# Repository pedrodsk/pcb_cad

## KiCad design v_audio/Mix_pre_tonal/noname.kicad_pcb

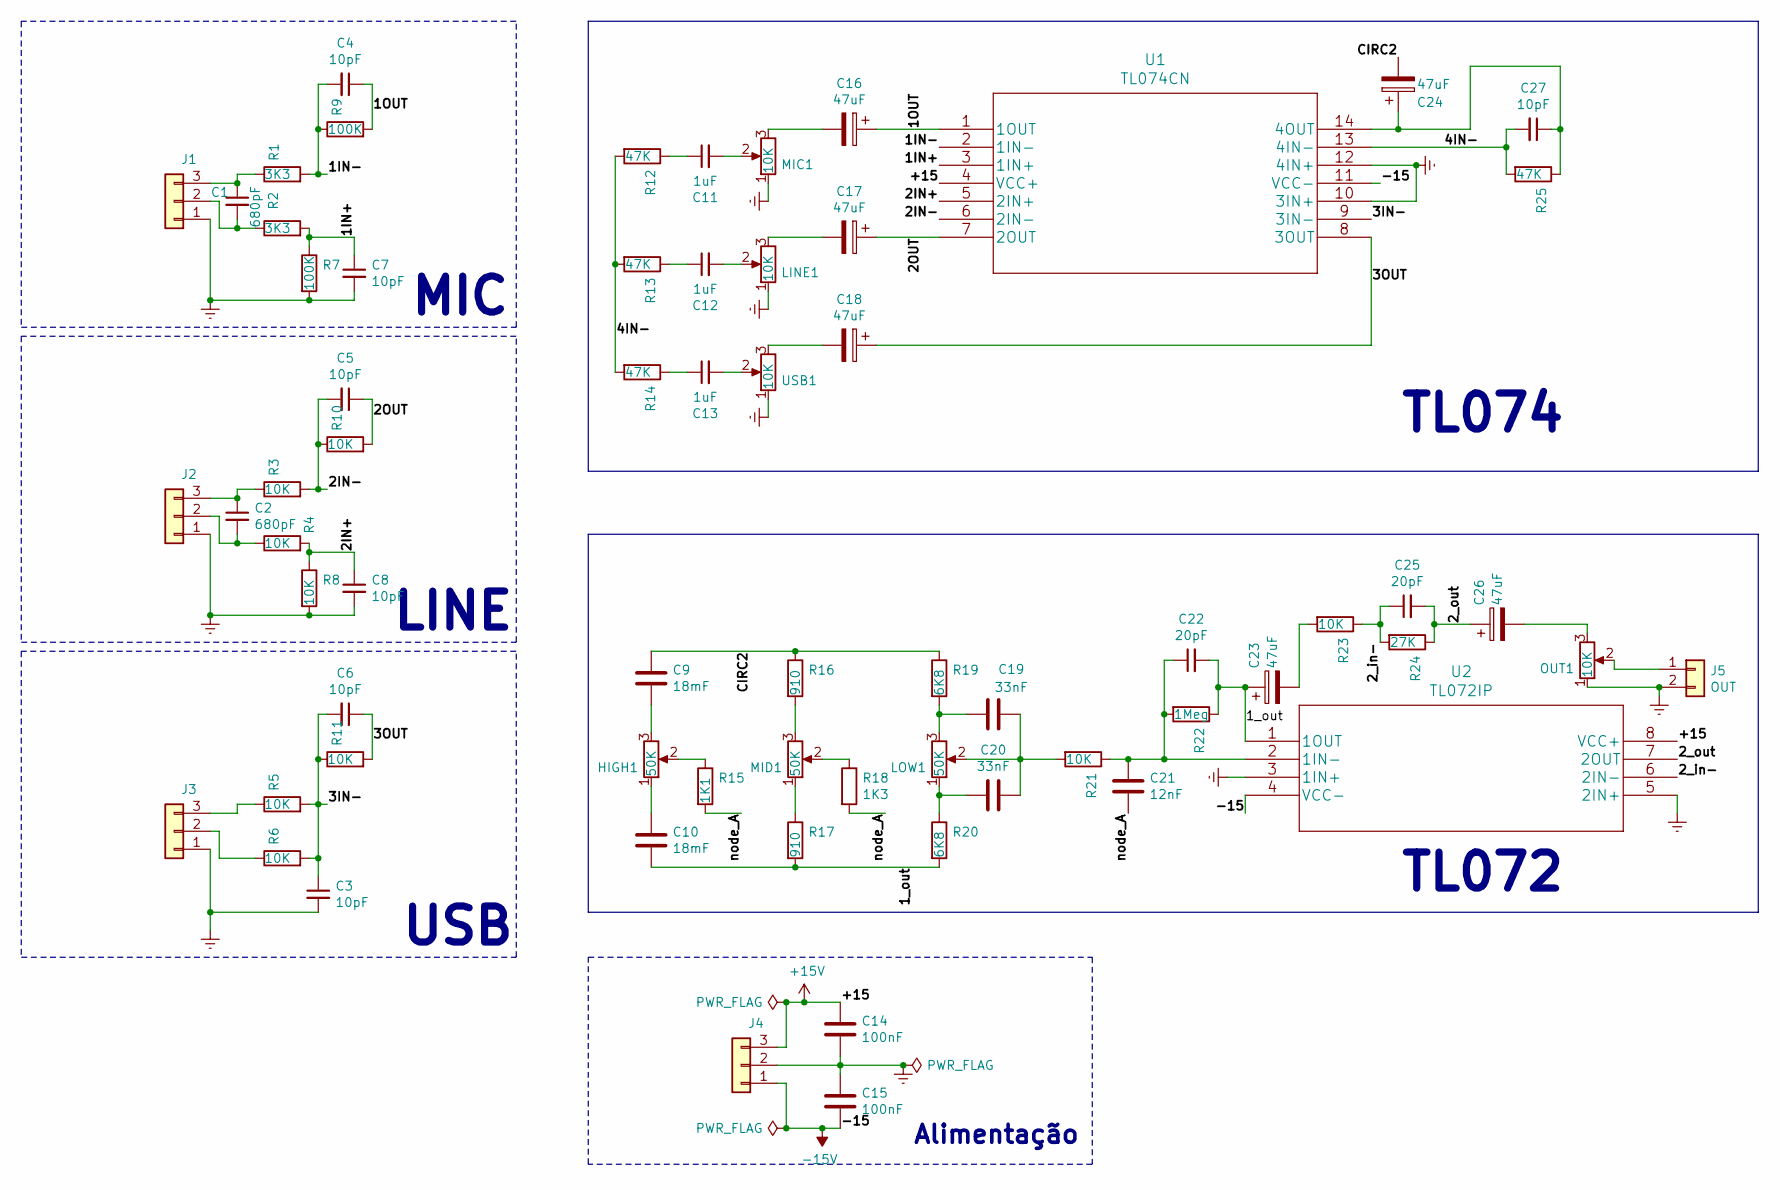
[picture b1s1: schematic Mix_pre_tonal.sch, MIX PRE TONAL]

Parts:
C1, C2: 680pF; C_Disc_D3.0mm_W1.6mm_P2.50mm
C3, C4, C5, C6, C7, C8, C27: 10pF; C_Disc_D3.0mm_W1.6mm_P2.50mm
C9, C10: 18mF; C_Disc_D7.0mm_W2.5mm_P5.00mm
C11, C12, C13: 1uF; C_Disc_D3.0mm_W1.6mm_P2.50mm
C14, C15: 100nF; C_Disc_D7.0mm_W2.5mm_P5.00mm
C16, C17, C18, C23, C24, C26: 47uF; CP_Radial_D4.0mm_P1.50mm
C19, C20: 33nF; C_Disc_D7.0mm_W2.5mm_P5.00mm
C21: 12nF; C_Disc_D7.0mm_W2.5mm_P5.00mm
C22, C25: 20pF; C_Disc_D3.0mm_W1.6mm_P2.50mm
HIGH1: 50K; Pot
J1: MIC; JST_NV_B03P-NV_1x03_P5.00mm_Vertical
J2: LINE; JST_NV_B03P-NV_1x03_P5.00mm_Vertical
J3: USB; JST_NV_B03P-NV_1x03_P5.00mm_Vertical
J4: Alimentação; JST_NV_B03P-NV_1x03_P5.00mm_Vertical
J5: OUT; JST_NV_B02P-NV_1x02_P5.00mm_Vertical
LINE1: 10K; Pot
LOW1: 50K; Pot
MIC1: 10K; Pot
MID1: 50K; Pot
OUT1: 10K; Pot
R1, R2: 3K3; R_Axial_DIN0207_L6.3mm_D2.5mm_P7.62mm_Horizontal
R3, R4, R5, R6, R8, R10, R11, R21, R23: 10K; R_Axial_DIN0207_L6.3mm_D2.5mm_P7.62mm_Horizontal
R7, R9: 100K; R_Axial_DIN0207_L6.3mm_D2.5mm_P7.62mm_Horizontal
R12, R13, R14, R25: 47K; R_Axial_DIN0207_L6.3mm_D2.5mm_P7.62mm_Horizontal
R15: 1K1; R_Axial_DIN0207_L6.3mm_D2.5mm_P7.62mm_Horizontal
R16, R17: 910; R_Axial_DIN0207_L6.3mm_D2.5mm_P7.62mm_Horizontal
R18: 1K3; R_Axial_DIN0207_L6.3mm_D2.5mm_P7.62mm_Horizontal
R19, R20: 6K8; R_Axial_DIN0207_L6.3mm_D2.5mm_P7.62mm_Horizontal
R22: 1Meg; R_Axial_DIN0207_L6.3mm_D2.5mm_P7.62mm_Horizontal
R24: 27K; R_Axial_DIN0207_L6.3mm_D2.5mm_P7.62mm_Horizontal
U1: TL074CN
U2: TL072IP
USB1: 10K; Pot

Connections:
+15V: C14.1, J4.3, U1.4 (VCC+), U2.8 (VCC+)
-15V: C15.2, J4.1, U1.11 (VCC-), U2.4 (VCC-)
/1IN+: C7.1, R2.2, R7.1, U1.3 (1IN+)
/1IN-: C4.2, R1.2, R9.1, U1.2 (1IN-)
/1OUT: C4.1, C16.1, R9.2, U1.1 (1OUT)
/1_out: C10.2, C22.2, C23.1, R17.2, R20.2, R22.1, U2.1 (1OUT)
/2IN+: C8.1, R4.2, R8.1, U1.5 (2IN+)
/2IN-: C5.2, R3.2, R10.1, U1.6 (2IN-)
/2OUT: C5.1, C17.1, R10.2, U1.7 (2OUT)
/2_in-: C25.1, R23.1, R24.2, U2.6 (2IN-)
/2_out: C25.2, C26.1, R24.1, U2.7 (2OUT)
/3IN-: C3.1, C6.2, R5.2, R6.2, R11.1, U1.9 (3IN-)
/3OUT: C6.1, C18.1, R11.2, U1.8 (3OUT)
/4IN-: C27.2, R12.2, R13.2, R14.2, R25.2, U1.13 (4IN-)
/node_A: C21.1, R15.2, R18.2
GNDREF: C3.2, C7.2, C8.2, C14.2, C15.1, J1.1, J2.1, J3.1, J4.2, J5.2, LINE1.1, MIC1.1, OUT1.1, R7.2, R8.2, U1.10 (3IN+), U1.12 (4IN+), U2.3 (1IN+), U2.5 (2IN+), USB1.1
unnamed: C1.1, J1.3, R1.1
unnamed: C1.2, J1.2, R2.1
unnamed: C2.1, J2.3, R3.1
unnamed: C2.2, J2.2, R4.1
unnamed: C9.2, HIGH1.3
unnamed: C10.1, HIGH1.1
unnamed: C11.1, R12.1
unnamed: C11.2, MIC1.2
unnamed: C12.1, R13.1
unnamed: C12.2, LINE1.2
unnamed: C13.1, R14.1
unnamed: C13.2, USB1.2
unnamed: C16.2, MIC1.3
unnamed: C17.2, LINE1.3
unnamed: C18.2, USB1.3
unnamed: C19.1, C20.1, LOW1.2, R21.2
unnamed: C19.2, LOW1.3, R19.2
unnamed: C20.2, LOW1.1, R20.1
unnamed: C21.2, C22.1, R21.1, R22.2, U2.2 (1IN-)
unnamed: C23.2, R23.2
unnamed: C26.2, OUT1.3
unnamed: HIGH1.2, R15.1
unnamed: J3.2, R6.1
unnamed: J3.3, R5.1
unnamed: J5.1, OUT1.2
unnamed: MID1.1, R17.1
unnamed: MID1.2, R18.1
unnamed: MID1.3, R16.2

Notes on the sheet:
MIC
LINE
USB
TL074
TL072
Alimentação

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
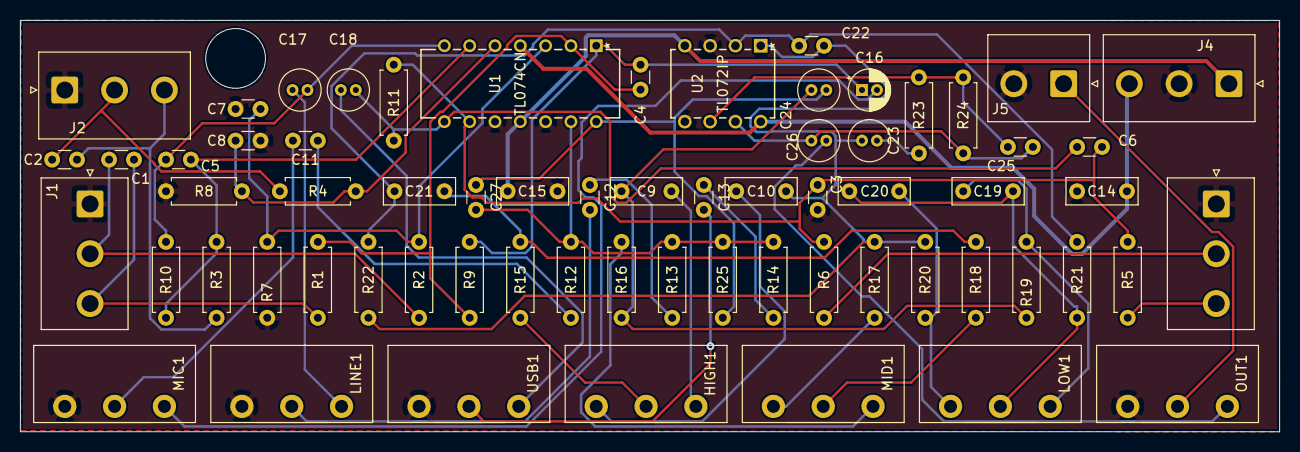
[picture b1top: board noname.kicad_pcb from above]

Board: 2 copper layers, 126.4 x 41.3 mm, 66 parts (0 on the bottom side), 46 nets.

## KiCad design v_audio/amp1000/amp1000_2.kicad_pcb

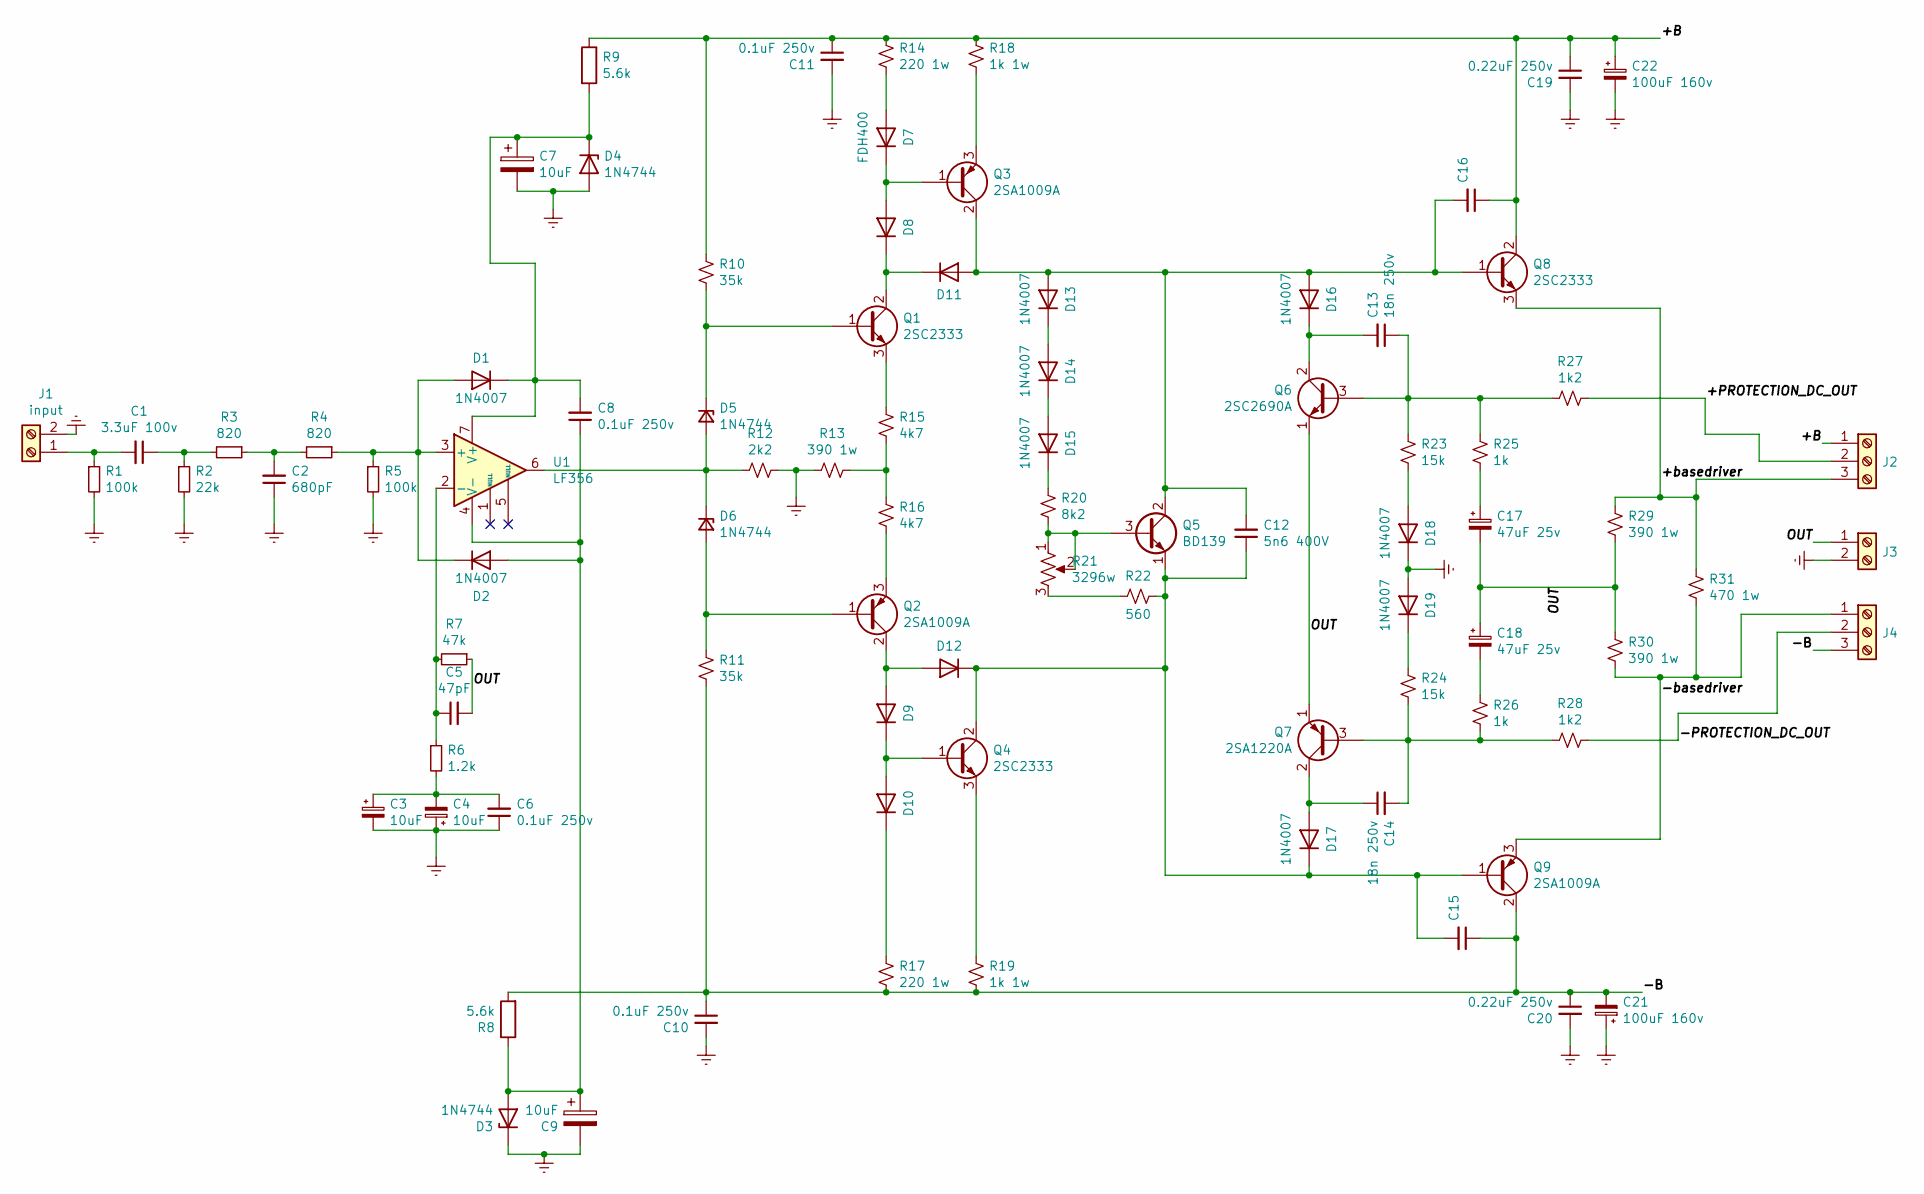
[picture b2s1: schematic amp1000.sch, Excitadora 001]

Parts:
C1: 3.3uF 100v; C_Axial_L22.0mm_D9.5mm_P27.50mm_Horizontal
C2: 680pF; C_Disc_D5.0mm_W2.5mm_P5.00mm
C3, C4, C7, C9: 10uF; CP_Radial_D4.0mm_P2.00mm
C5: 47pF; C_Disc_D5.0mm_W2.5mm_P5.00mm
C6, C8: 0.1uF 250v; C_Disc_D5.0mm_W2.5mm_P5.00mm
C10, C11: 0.1uF 250v; C_Disc_D7.5mm_W5.0mm_P10.00mm
C12: 5n6 400V; C_Disc_D5.0mm_W2.5mm_P5.00mm
C13, C14: 18n 250v; C_Disc_D5.0mm_W2.5mm_P5.00mm
C15, C16: 0.22uF 250v; C_Disc_D5.0mm_W2.5mm_P5.00mm
C17, C18: 47uF 25v; CP_Radial_D8.0mm_P3.50mm
C19, C20: 0.22uF 250v; C_Disc_D7.5mm_W5.0mm_P10.00mm
C21, C22: 100uF 160v; CP_Radial_D10.0mm_P5.00mm
D1, D2, D8, D9, D10, D11, D12, D13, D14, D15, D16, D17, D18, D19: 1N4007; D_A-405_P7.62mm_Horizontal
D3, D4, D5, D6: 1N4744; D_A-405_P7.62mm_Horizontal
D7: FDH400; D_A-405_P7.62mm_Horizontal
J1: input; TerminalBlock_bornier-2_P5.08mm
J2, J4: Screw_Terminal_01x03; TerminalBlock_bornier-3_P5.08mm
J3: Screw_Terminal_01x02; TerminalBlock_bornier-2_P5.08mm
Q1, Q4: 2SC2333; TO-220-3_Vertical
Q2, Q3: 2SA1009A; TO-220-3_Vertical
Q5: BD139; TO-126-3_Vertical
Q6: 2SC2690A; TO-126-3_Vertical
Q7: 2SA1220A; TO-126-3_Vertical
Q8: 2SC2333; TO-220-3_Horizontal_TabDown
Q9: 2SA1009A; TO-220-3_Horizontal_TabDown
R1, R5: 100k; R_Axial_DIN0207_L6.3mm_D2.5mm_P7.62mm_Horizontal
R2: 22k; R_Axial_DIN0207_L6.3mm_D2.5mm_P7.62mm_Horizontal
R3, R4: 820; R_Axial_DIN0207_L6.3mm_D2.5mm_P7.62mm_Horizontal
R6: 1.2k; R_Axial_DIN0207_L6.3mm_D2.5mm_P7.62mm_Horizontal
R7: 47k; R_Axial_DIN0207_L6.3mm_D2.5mm_P7.62mm_Horizontal
R8, R9: 5.6k; R_Axial_DIN0207_L6.3mm_D2.5mm_P7.62mm_Horizontal
R10, R11: 35k; R_Axial_DIN0207_L6.3mm_D2.5mm_P7.62mm_Horizontal
R12: 2k2; R_Axial_DIN0207_L6.3mm_D2.5mm_P7.62mm_Horizontal
R13, R29, R30: 390 1w; R_Axial_DIN0207_L6.3mm_D2.5mm_P7.62mm_Horizontal
R14, R17: 220 1w; R_Axial_DIN0207_L6.3mm_D2.5mm_P7.62mm_Horizontal
R15, R16: 4k7; R_Axial_DIN0207_L6.3mm_D2.5mm_P7.62mm_Horizontal
R18, R19: 1k 1w; R_Axial_DIN0207_L6.3mm_D2.5mm_P7.62mm_Horizontal
R20: 8k2; R_Axial_DIN0207_L6.3mm_D2.5mm_P7.62mm_Horizontal
R21: 3296w; Potentiometer_Bourns_3296W_Vertical
R22: 560; R_Axial_DIN0207_L6.3mm_D2.5mm_P7.62mm_Horizontal
R23, R24: 15k; R_Axial_DIN0207_L6.3mm_D2.5mm_P7.62mm_Horizontal
R25, R26: 1k; R_Axial_DIN0207_L6.3mm_D2.5mm_P7.62mm_Horizontal
R27, R28: 1k2; R_Axial_DIN0207_L6.3mm_D2.5mm_P7.62mm_Horizontal
R31: 470 1w; R_Axial_DIN0207_L6.3mm_D2.5mm_P7.62mm_Horizontal
U1: LF356; DIP-8_W7.62mm

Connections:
/+B: C11.1, C16.1, C19.1, C22.1, J2.1, Q8.2 (C), R9.1, R10.2, R14.2, R18.2
/+PROTECTION_DC_OUT: J2.2, R27.2
/+basedriver: J2.3, Q8.3 (E), R29.2, R31.2
/-B: C10.1, C15.1, C20.1, C21.2, J4.3, Q9.2 (C), R8.2, R11.1, R17.1, R19.1
/-PROTECTION_DC_OUT: J4.2, R28.2
/-basedriver: J4.1, Q9.3 (E), R30.1, R31.1
/OUT: C5.2, C17.2, C18.1, J3.1, Q6.1 (E), Q7.1 (E), R7.1, R29.1, R30.2
Earth: C2.1, C3.2, C4.1, C6.1, C7.2, C9.2, C10.2, C11.2, C19.2, C20.2, C21.1, C22.2, D3.1 (K), D4.2 (A), D18.1 (K), D19.2 (A), J1.2, J3.2, R1.2, R2.2, R5.2, R12.1, R13.2
unnamed: C1.1, R2.1, R3.2
unnamed: C1.2, J1.1, R1.1
unnamed: C2.2, R3.1, R4.2
unnamed: C3.1, C4.2, C6.2, R6.2
unnamed: C5.1, R6.1, R7.2, U1.2 (-)
unnamed: C7.1, C8.2, D1.1 (K), D4.1 (K), R9.2, U1.7 (V+)
unnamed: C8.1, C9.1, D2.2 (A), D3.2 (A), R8.1, U1.4 (V-)
unnamed: C12.1, C15.2, D12.1 (K), D17.1 (K), Q4.2 (C), Q5.1 (E), Q9.1 (B), R22.1
unnamed: C12.2, C16.2, D11.2 (A), D13.2 (A), D16.2 (A), Q3.2 (C), Q5.2 (C), Q8.1 (B)
unnamed: C13.1, Q6.3 (B), R23.2, R25.2, R27.1
unnamed: C13.2, D16.1 (K), Q6.2 (C)
unnamed: C14.1, D17.2 (A), Q7.2 (C)
unnamed: C14.2, Q7.3 (B), R24.1, R26.1, R28.1
unnamed: C17.1, R25.1
unnamed: C18.2, R26.2
unnamed: D1.2 (A), D2.1 (K), R4.1, R5.1, U1.3 (+)
unnamed: D5.1 (K), Q1.1 (B), R10.1
unnamed: D5.2 (A), D6.1 (K), R12.2, U1.6
unnamed: D6.2 (A), Q2.1 (B), R11.2
unnamed: D7.1 (K), D8.2 (A), Q3.1 (B)
unnamed: D7.2 (A), R14.1
unnamed: D10.1 (K), R17.2
unnamed: D9.1 (K), D10.2 (A), Q4.1 (B)
unnamed: D8.1 (K), D11.1 (K), Q1.2 (C)
unnamed: D9.2 (A), D12.2 (A), Q2.2 (C)
unnamed: D13.1 (K), D14.2 (A)
unnamed: D14.1 (K), D15.2 (A)
unnamed: D15.1 (K), R20.2
unnamed: D18.2 (A), R23.1
unnamed: D19.1 (K), R24.2
unnamed: Q1.3 (E), R15.2
unnamed: Q2.3 (E), R16.1
unnamed: Q3.3 (E), R18.1
unnamed: Q4.3 (E), R19.2
unnamed: Q5.3 (B), R20.1, R21.1, R21.2
unnamed: R13.1, R15.1, R16.2
unnamed: R21.3, R22.2

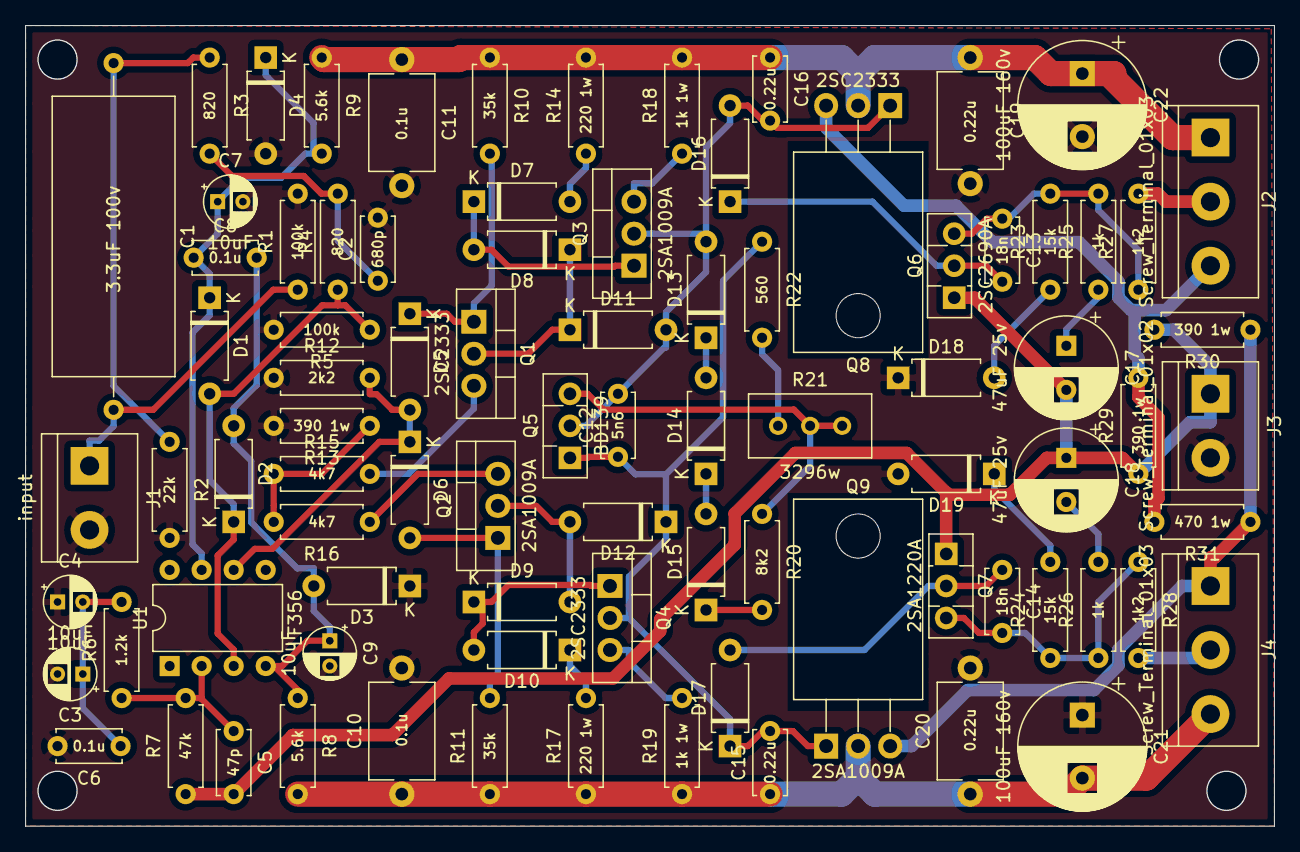
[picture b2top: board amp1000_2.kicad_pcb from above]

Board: 2 copper layers, 99.1 x 63.5 mm, 86 parts (0 on the bottom side), 45 nets.
